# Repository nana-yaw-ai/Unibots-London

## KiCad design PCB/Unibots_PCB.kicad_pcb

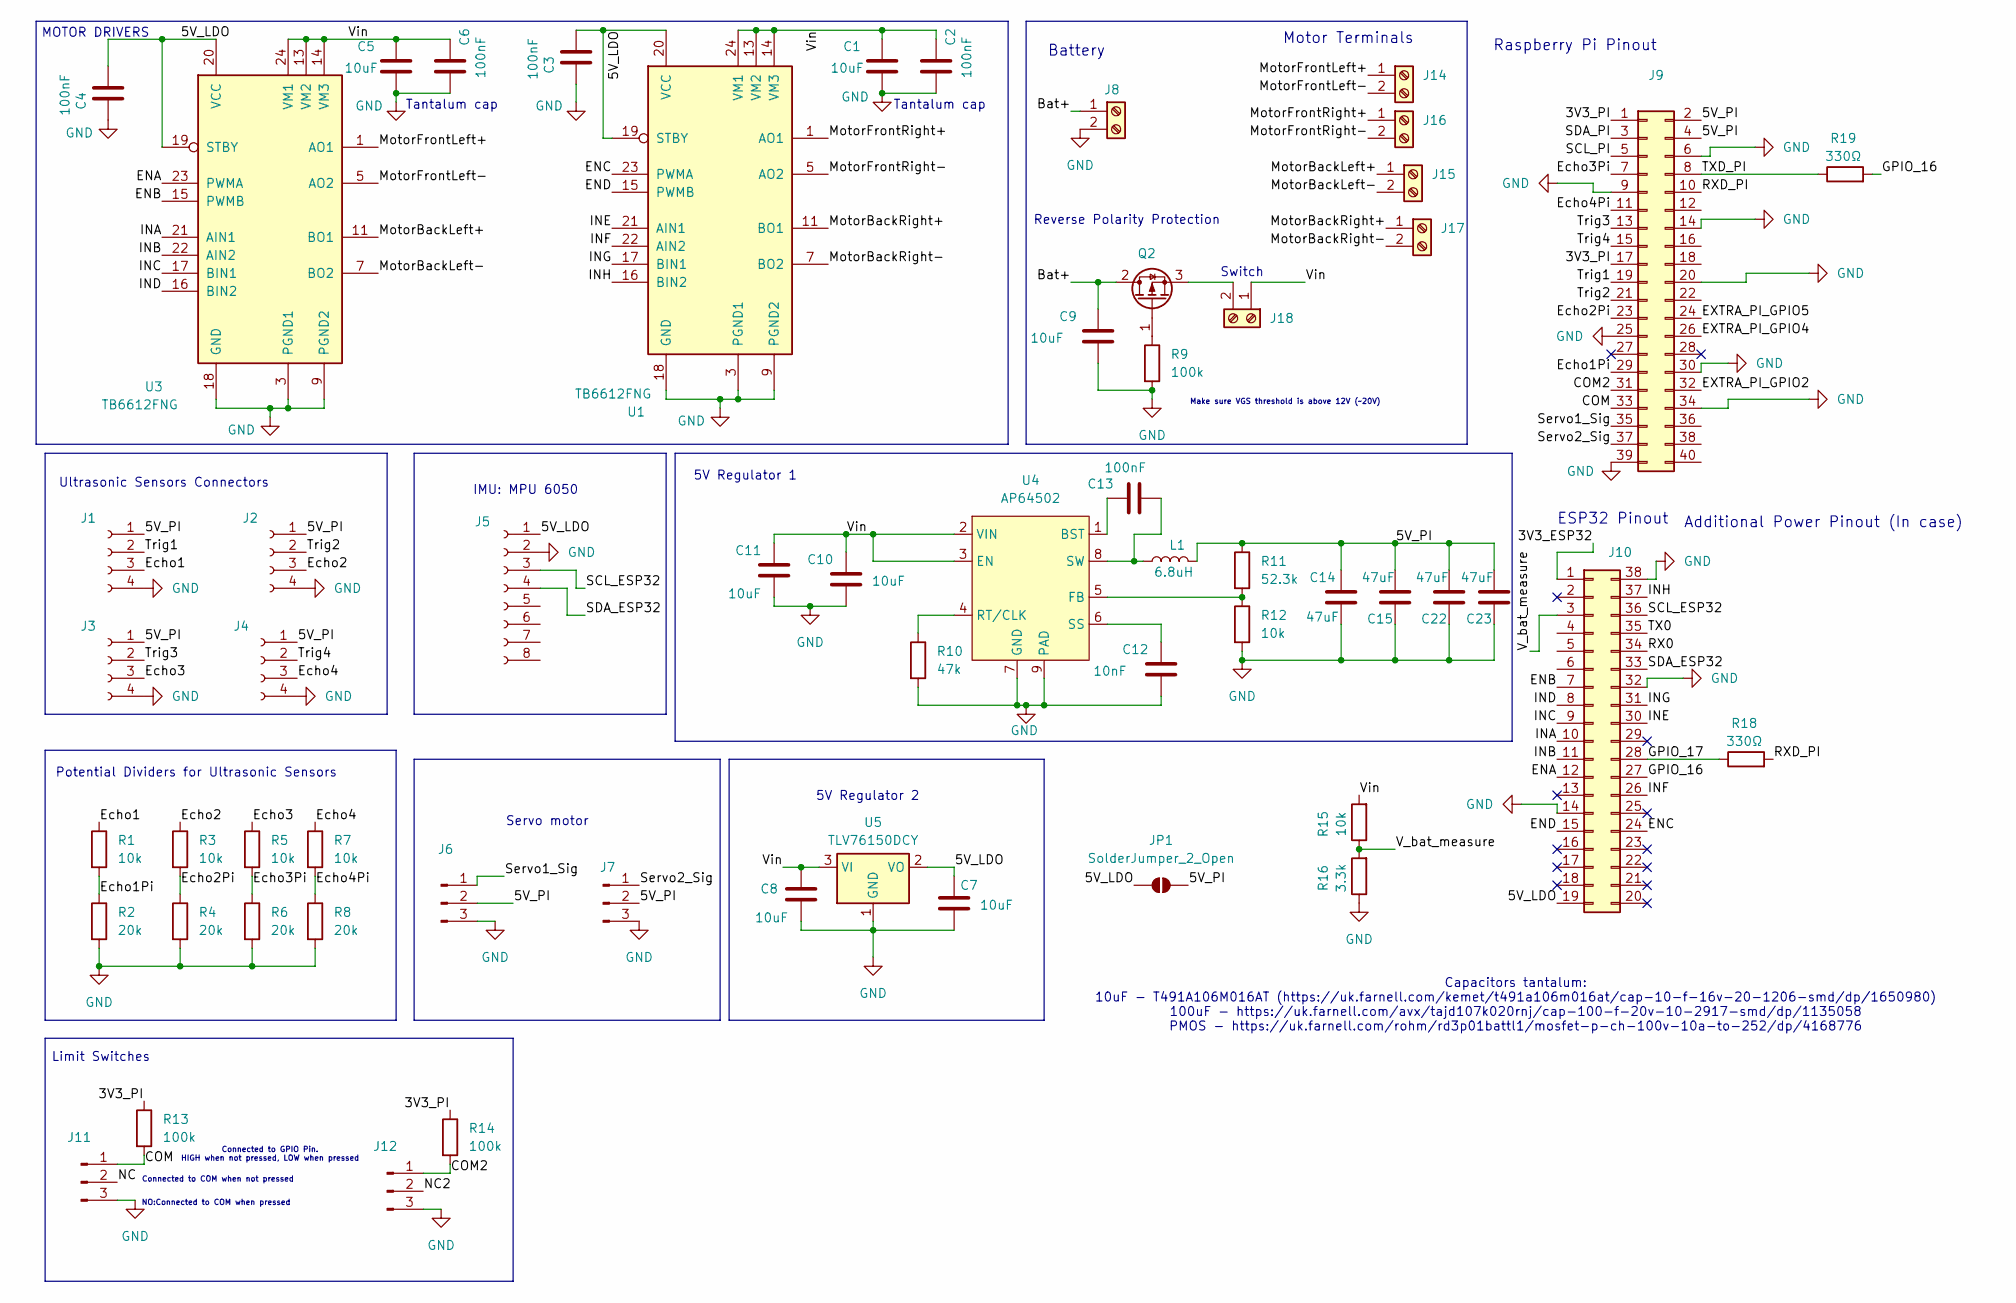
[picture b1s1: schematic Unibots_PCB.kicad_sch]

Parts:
C1, C5, C7, C8, C9, C10, C11: 10uF; C_0805_2012Metric_Pad1.18x1.45mm_HandSolder
C2, C3, C4, C6, C13: 100nF; C_0805_2012Metric_Pad1.18x1.45mm_HandSolder
C12: 10nF; C_0805_2012Metric_Pad1.18x1.45mm_HandSolder
C14, C15, C22, C23: 47uF; C_1206_3216Metric_Pad1.33x1.80mm_HandSolder
J1, J2, J3, J4: Conn_01x04_Socket; PinSocket_1x04_P2.54mm_Vertical
J5: Conn_01x08_Socket; PinHeader_1x08_P2.54mm_Vertical
J6, J7, J11, J12: Conn_01x03_Pin; PinSocket_1x03_P2.54mm_Vertical
J8, J14, J15, J16, J17, J18: Screw_Terminal_01x02; TerminalBlock_MaiXu_MX126-5.0-02P_1x02_P5.00mm
J9: Conn_02x20_Odd_Even; IDC-Header_2x20_P2.54mm_Vertical
J10: Conn_02x19_Counter_Clockwise; ESP32_DevkitC_V4
JP1: SolderJumper_2_Open; SolderJumper-2_P1.3mm_Open_TrianglePad1.0x1.5mm
L1: 6.8uH; L_Coilcraft_XAL5020-XXX
Q2: RD3P01BATTL1; TO-252-3_TabPin2
R1, R3, R5, R7, R12, R15: 10k; R_0805_2012Metric_Pad1.20x1.40mm_HandSolder
R2, R4, R6, R8: 20k; R_0805_2012Metric_Pad1.20x1.40mm_HandSolder
R9, R13, R14: 100k; R_0805_2012Metric_Pad1.20x1.40mm_HandSolder
R10: 47k; R_0805_2012Metric_Pad1.20x1.40mm_HandSolder
R11: 52.3k; R_0805_2012Metric_Pad1.20x1.40mm_HandSolder
R16: 3.3k; R_0805_2012Metric_Pad1.20x1.40mm_HandSolder
R18, R19: 330Ω; R_0805_2012Metric_Pad1.20x1.40mm_HandSolder
U1, U3: TB6612FNG; SSOP-24_5.3x8.2mm_P0.65mm
U4: AP64502; Diodes_SO-8EP
U5: TLV76150DCY; SOT-223-3_TabPin2

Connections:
/3V3_ESP32: J10.1
/3V3_PI: J9.1, J9.17, R13.1, R14.1
/5V_LDO: C3.1, C4.1, C7.2, J5.1, J10.19, JP1.1 (A), U1.19 (STBY), U1.20 (VCC), U3.19 (STBY), U3.20 (VCC), U5.2 (VO)
/5V_PI: C14.2, C15.2, C22.2, C23.2, J1.1, J2.1, J3.1, J4.1, J6.2, J7.2, J9.2, J9.4, JP1.2 (B), L1.2, R11.1
/Bat+: C9.2, J8.1, Q2.2 (D)
/COM: J9.33, J11.1, R13.2
/COM2: J9.31, J12.1, R14.2
/ENA: J10.12, U3.23 (PWMA)
/ENB: J10.7, U3.15 (PWMB)
/ENC: J10.24, U1.23 (PWMA)
/END: J10.15, U1.15 (PWMB)
/EXTRA_PI_GPIO2: J9.32
/EXTRA_PI_GPIO4: J9.26
/EXTRA_PI_GPIO5: J9.24
/Echo1: J1.3, R1.1
/Echo1Pi: J9.29, R1.2, R2.1
/Echo2: J2.3, R3.1
/Echo2Pi: J9.23, R3.2, R4.1
/Echo3: J3.3, R5.1
/Echo3Pi: J9.7, R5.2, R6.1
/Echo4: J4.3, R7.1
/Echo4Pi: J9.11, R7.2, R8.1
/GPIO_16: J10.27, R19.2
/GPIO_17: J10.28, R18.1
/INA: J10.10, U3.21 (AIN1)
/INB: J10.11, U3.22 (AIN2)
/INC: J10.9, U3.17 (BIN1)
/IND: J10.8, U3.16 (BIN2)
/INE: J10.30, U1.21 (AIN1)
/INF: J10.26, U1.22 (AIN2)
/ING: J10.31, U1.17 (BIN1)
/INH: J10.37, U1.16 (BIN2)
/MotorBackLeft+: J15.1, U3.11 (BO1), U3.12 (BO1)
/MotorBackLeft-: J15.2, U3.7 (BO2), U3.8 (BO2)
/MotorBackRight+: J17.1, U1.11 (BO1), U1.12 (BO1)
/MotorBackRight-: J17.2, U1.7 (BO2), U1.8 (BO2)
/MotorFrontLeft+: J14.1, U3.1 (AO1), U3.2 (AO1)
/MotorFrontLeft-: J14.2, U3.5 (AO2), U3.6 (AO2)
/MotorFrontRight+: J16.1, U1.1 (AO1), U1.2 (AO1)
/MotorFrontRight-: J16.2, U1.5 (AO2), U1.6 (AO2)
/NC: J11.2
/NC2: J12.2
/RX0: J10.34
/RXD_PI: J9.10, R18.2
/SCL_ESP32: J5.3, J10.36
/SCL_PI: J9.5
/SDA_ESP32: J5.4, J10.33
/SDA_PI: J9.3
/Servo1_Sig: J6.1, J9.35
/Servo2_Sig: J7.1, J9.37
/TX0: J10.35
/TXD_PI: J9.8, R19.1
/Trig1: J1.2, J9.19
/Trig2: J2.2, J9.21
/Trig3: J3.2, J9.13
/Trig4: J4.2, J9.15
/V_bat_measure: J10.3, R15.1, R16.2
/Vin: C1.2, C2.2, C5.2, C6.2, C8.2, C10.2, C11.2, J18.1, R15.2, U1.13 (VM2), U1.14 (VM3), U1.24 (VM1), U3.13 (VM2), U3.14 (VM3), U3.24 (VM1), U4.2 (VIN), U4.3 (EN), U5.3 (VI)
GND: C1.1, C2.1, C3.2, C4.2, C5.1, C6.1, C7.1, C8.1, C9.1, C10.1, C11.1, C12.1, C14.1, C15.1, C22.1, C23.1, J1.4, J2.4, J3.4, J4.4, J5.2, J6.3, J7.3, J8.2, J9.6, J9.9, J9.14, J9.20, J9.25, J9.30, J9.34, J9.39, J10.14, J10.32, J10.38, J11.3, J12.3, R2.2, R4.2, R6.2, R8.2, R9.2, R10.2, R12.2, R16.1, U1.3 (PGND1), U1.4 (PGND1), U1.9 (PGND2), U1.10 (PGND2), U1.18 (GND), U3.3 (PGND1), U3.4 (PGND1), U3.9 (PGND2), U3.10 (PGND2), U3.18 (GND), U4.7 (GND), U4.9 (PAD), U5.1 (GND)
unnamed: J18.2, Q2.3 (S)
unnamed: Q2.1 (G), R9.1
unnamed: C13.2, U4.1 (BST)
unnamed: R11.2, R12.1, U4.5 (FB)
unnamed: R10.1, U4.4 (RT/CLK)
unnamed: C12.2, U4.6 (SS)
unnamed: C13.1, L1.1, U4.8 (SW)

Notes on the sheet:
Servo motor
Tantalum cap
Potential Dividers for Ultrasonic Sensors
Capacitors tantalum: 10uF - T491A106M016AT (https://uk.farnell.com/kemet/t491a106m016at/cap-10-f-16v-20-1206-smd/dp/1650980) 100uF - https://uk.farnell.com/avx/tajd107k020rnj/cap-100-f-20v-10-2917-smd/dp/1135058 PMOS - https://uk.farnell.com/rohm/rd3p01battl1/mosfet-p-ch-100v-10a-to-252/dp/4168776
IMU: MPU 6050
ESP32 Pinout
Switch
Raspberry Pi Pinout
Battery
Connected to GPIO Pin. HIGH when not pressed, LOW when pressed
Additional Power Pinout (In case)
5V Regulator 1
Limit Switches
Reverse Polarity Protection
Motor Terminals
Ultrasonic Sensors Connectors
NO:Connected to COM when pressed
MOTOR DRIVERS
5V Regulator 2
Make sure VGS threshold is above 12V (~20V)
Connected to COM when not pressed

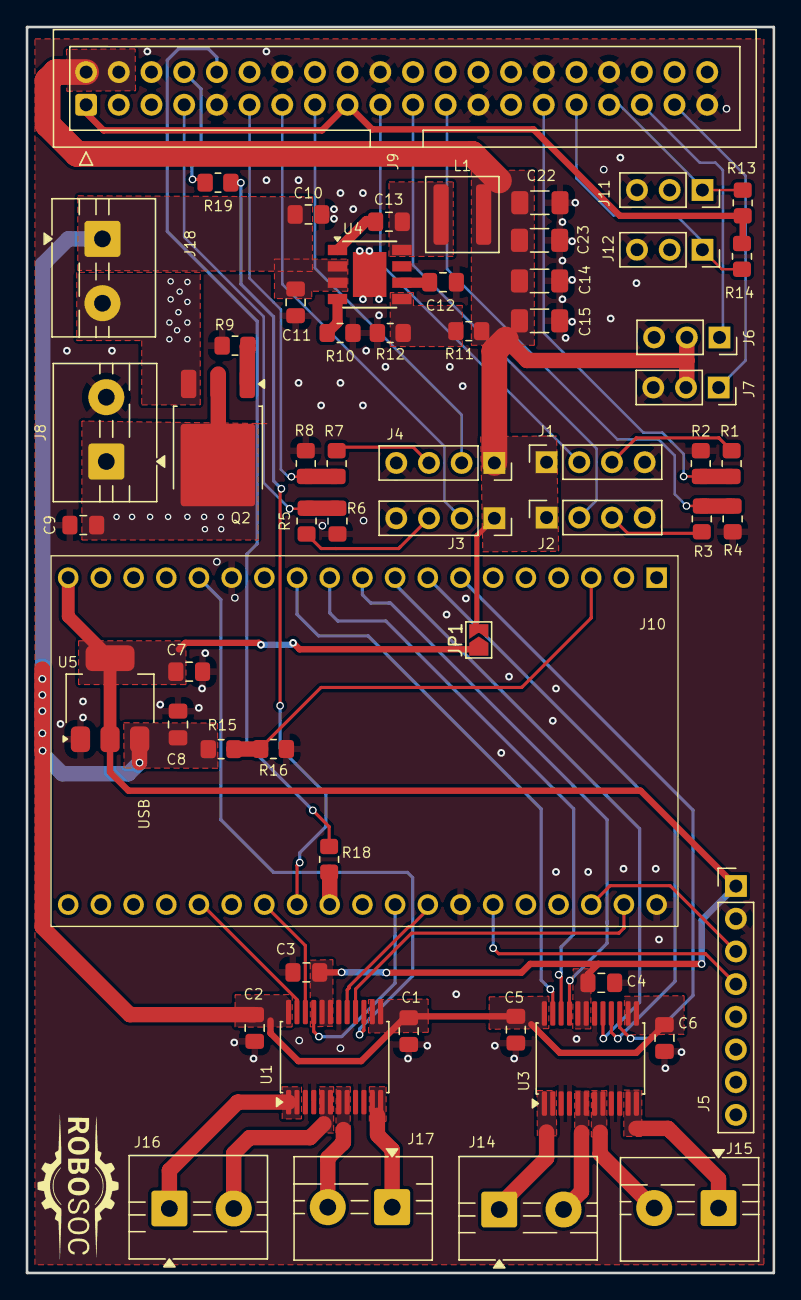
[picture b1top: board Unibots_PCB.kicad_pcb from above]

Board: 2 copper layers, 58.0 x 96.8 mm, 59 parts (0 on the bottom side), 56 nets.

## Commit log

2026-03-22 Initial KiCad project
2026-03-22 Add KiCad gitignore
2026-03-22 Apply gitignore cleanup
2026-03-22 Move KiCad project into pcb folder
2026-03-22 add readme to repo
2026-03-25 add excel tracker
2026-03-26 change 1
2026-03-28 add new components
2026-04-01 Most schematic layout
2026-04-05 change
2026-04-05 pcb update
2026-04-06 pcb design update
